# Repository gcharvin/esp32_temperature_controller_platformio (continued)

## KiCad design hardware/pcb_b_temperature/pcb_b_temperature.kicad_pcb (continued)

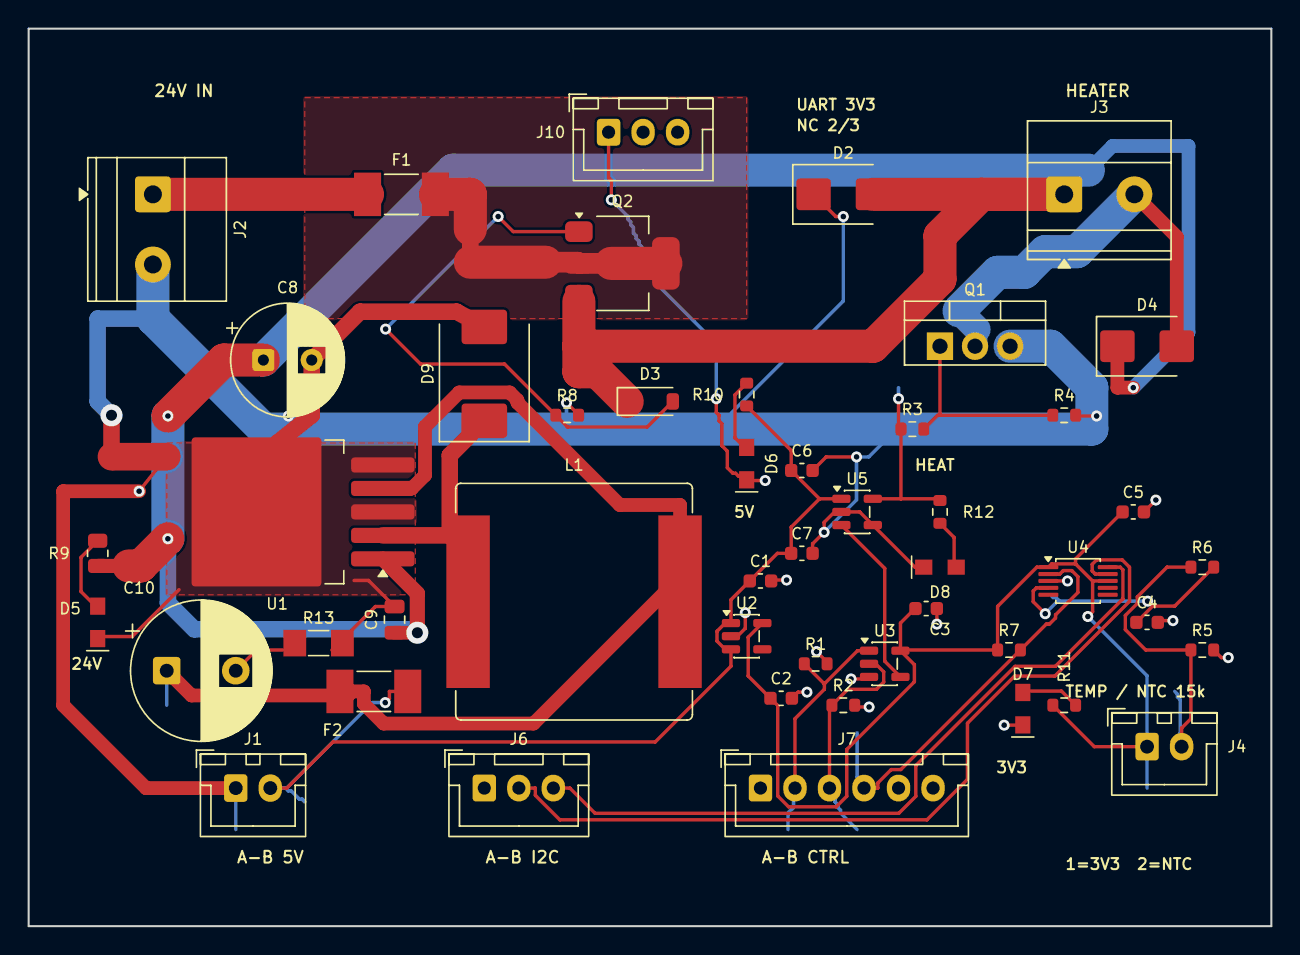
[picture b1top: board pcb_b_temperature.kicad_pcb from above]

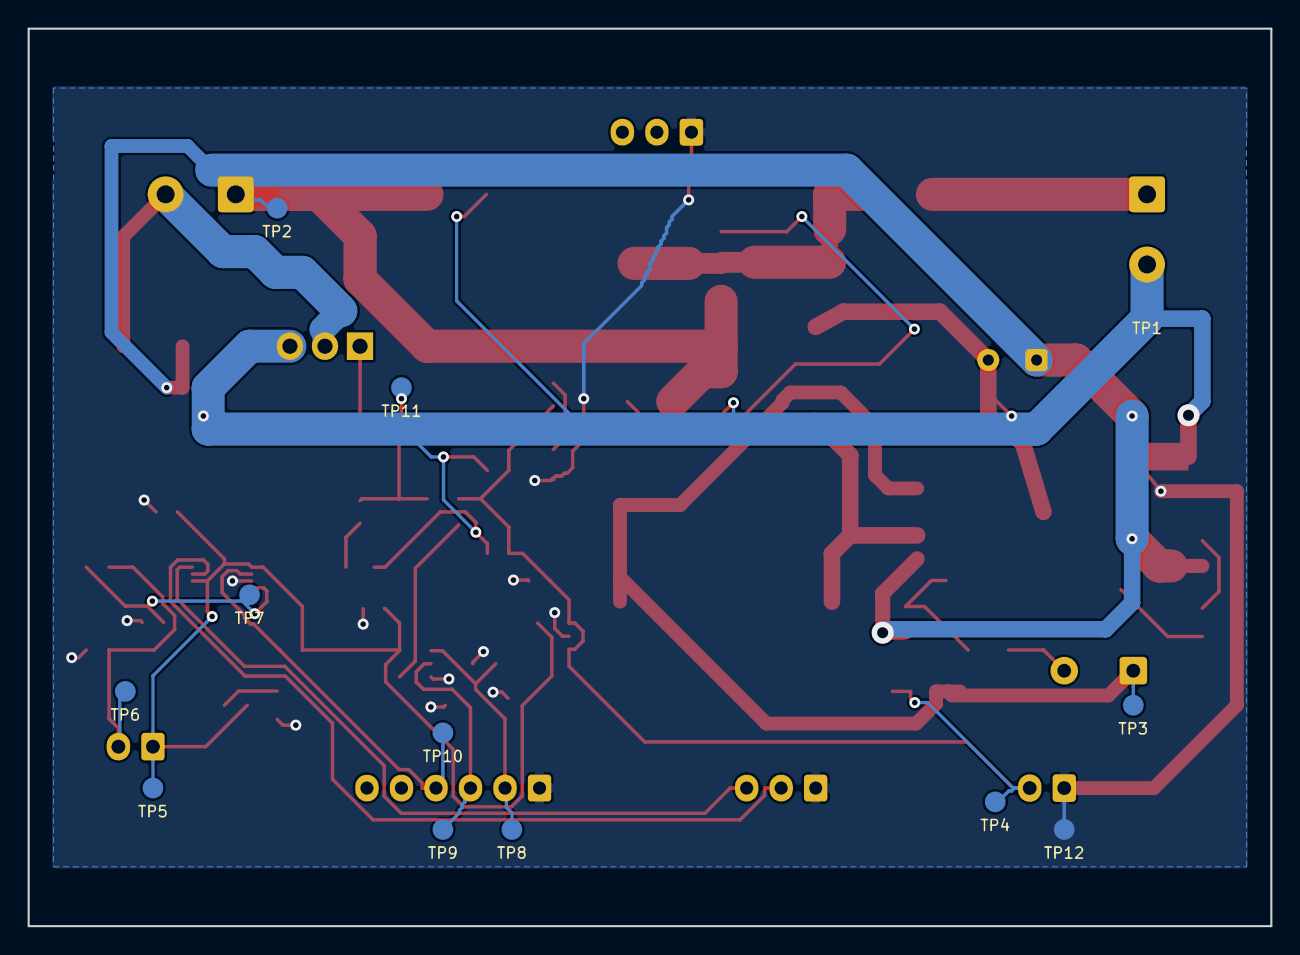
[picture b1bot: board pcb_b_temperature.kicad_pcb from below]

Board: 2 copper layers, 90.0 x 65.0 mm, 61 parts (12 on the bottom side), 26 nets.

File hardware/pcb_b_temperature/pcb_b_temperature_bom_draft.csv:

Reference,Value,Footprint,Design_Status,MPN,Manufacturer
C1,1uF / 16V X7R,Capacitor_SMD:C_0603_1608Metric,ENGINEERING_SELECTED_STOCK_REVISION_2026_11_10,0603B105K160CT,Walsin
C2,1uF / 10V X7R,Capacitor_SMD:C_0603_1608Metric,ENGINEERING_SELECTED_STOCK_REVISION_2026_11_10,0603B105K160CT,Walsin
C3,100nF / 10V X7R,Capacitor_SMD:C_0603_1608Metric,ENGINEERING_SELECTED_FOR_PROTOTYPE,C0603C104K4RACTU,KEMET / Yageo Group
C4,100nF / 10V X7R,Capacitor_SMD:C_0603_1608Metric,ENGINEERING_SELECTED_FOR_PROTOTYPE,C0603C104K4RACTU,KEMET / Yageo Group
C5,100nF / 10V X7R,Capacitor_SMD:C_0603_1608Metric,ENGINEERING_SELECTED_FOR_PROTOTYPE,C0603C104K4RACTU,KEMET / Yageo Group
C6,100nF / 16V X7R,Capacitor_SMD:C_0603_1608Metric,ENGINEERING_SELECTED_FOR_PROTOTYPE,C0603C104K4RACTU,KEMET / Yageo Group
C7,1uF / 16V X7R,Capacitor_SMD:C_0603_1608Metric,ENGINEERING_SELECTED_STOCK_REVISION_2026_11_10,0603B105K160CT,Walsin
C8,100uF / 50V / EEUFR1H101,Capacitor_THT:CP_Radial_D8.0mm_P3.50mm,ENGINEERING_SELECTED_FOR_PROTOTYPE,EEUFR1H101,Panasonic
C9,100nF / 50V X7R,Capacitor_SMD:C_0805_2012Metric,ENGINEERING_SELECTED_FOR_PROTOTYPE,C0805C104K5RACTU,KEMET / Yageo Group
C10,330uF / 35V,LabHardware:CP_Radial_EEUFS1V331LB_P5_D10_Keepout,ENGINEERING_SELECTED_STOCK_REVISION_2026_11_10,EEUFS1V331LB,Panasonic
D2,SMBJ24CA / transients NOT qualified,Diode_SMD:D_SMB,ENGINEERING_SELECTED_FOR_PROTOTYPE,SMBJ24CA,Littelfuse
D3,BZT52C12 / 12V gate clamp,Diode_SMD:D_SOD-123,ENGINEERING_SELECTED_FOR_PROTOTYPE,BZT52C12-7-F,Diodes Incorporated
D4,STPS5L60U / cable flyback,Diode_SMD:D_SMB,ENGINEERING_SELECTED_FOR_PROTOTYPE,STPS5L60U,STMicroelectronics
D5,APT2012LZGCK,LabHardware:LED_Kingbright_APT2012_Manufacturer,ENGINEERING_SELECTED_FOR_PROTOTYPE,APT2012LZGCK,Kingbright
D6,APT2012LZGCK,LabHardware:LED_Kingbright_APT2012_Manufacturer,ENGINEERING_SELECTED_FOR_PROTOTYPE,APT2012LZGCK,Kingbright
D7,APT2012LZGCK,LabHardware:LED_Kingbright_APT2012_Manufacturer,ENGINEERING_SELECTED_FOR_PROTOTYPE,APT2012LZGCK,Kingbright
D8,APT2012LSYCK/J3-PRV,LabHardware:LED_Kingbright_APT2012_Manufacturer,ENGINEERING_SELECTED_STOCK_REVISION_2026_11_10,APT2012LSYCK/J3-PRV,Kingbright
D9,SS36 / 60V 3A,Diode_SMD:D_SMC,ENGINEERING_SELECTED_FOR_PROTOTYPE,SS36-E3/57T,Vishay
F1,6.3A / 125VDC / 045106.3MRL,Fuse:Fuse_Littelfuse-NANO2-451_453,ENGINEERING_SELECTED_FOR_PROTOTYPE,045106.3MRL,Littelfuse
F2,1A / 125VDC / 0451001.MRL,Fuse:Fuse_Littelfuse-NANO2-451_453,ENGINEERING_SELECTED_FOR_PROTOTYPE,0451001.MRL,Littelfuse
J1,A-B POWER / XH-2,Connector_JST:JST_XH_B2B-XH-A_1x02_P2.50mm_Vertical,ENGINEERING_SELECTED_FOR_PROTOTYPE,B2B-XH-A(LF)(SN),JST
J2,24V IN / + PGND,"TerminalBlock_Phoenix:TerminalBlock_Phoenix_MKDS-1,5-2-5.08_1x02_P5.08mm_Horizontal",ENGINEERING_SELECTED_FOR_PROTOTYPE,1715721,Phoenix Contact
J3,HEATER / + switched return,"TerminalBlock_Phoenix:TerminalBlock_Phoenix_MKDS-1,5-2-5.08_1x02_P5.08mm_Horizontal",ENGINEERING_SELECTED_FOR_PROTOTYPE,1715721,Phoenix Contact
J4,TEMP / NTC 15k B3920,Connector_JST:JST_XH_B2B-XH-A_1x02_P2.50mm_Vertical,ENGINEERING_SELECTED_FOR_PROTOTYPE,B2B-XH-A(LF)(SN),JST
J6,A-B I2C / XH-3,Connector_JST:JST_XH_B3B-XH-A_1x03_P2.50mm_Vertical,ENGINEERING_SELECTED_FOR_PROTOTYPE,B3B-XH-A(LF)(SN),JST
J7,A-B CTRL / XH-6,Connector_JST:JST_XH_B6B-XH-A_1x06_P2.50mm_Vertical,ENGINEERING_SELECTED_FOR_PROTOTYPE,B6B-XH-A(LF)(SN),JST
L1,100uH / SRP1770TA-101M,Inductor_SMD:L_Bourns_SRP1770TA_16.9x16.9mm,ENGINEERING_SELECTED_FOR_PROTOTYPE,SRP1770TA-101M,Bourns
NT1,GND STAR / NO COMPONENT,NetTie:NetTie-2_SMD_Pad2.0mm,NOT_A_FACTORY_PURCHASED_NATIVE_PART,,
Q1,IRLZ44NPBF / gate 5 V,Package_TO_SOT_THT:TO-220-3_Vertical,ENGINEERING_SELECTED_FOR_PROTOTYPE,IRLZ44NPBF,Infineon
Q2,DMP6023LE-13 / reverse input,Package_TO_SOT_SMD:SOT-223-3_TabPin2,ENGINEERING_SELECTED_FOR_PROTOTYPE,DMP6023LE-13,Diodes Incorporated
R1,47k,Resistor_SMD:R_0603_1608Metric,ENGINEERING_SELECTED_FOR_PROTOTYPE,RC0603FR-0747KL,YAGEO
R2,47k,Resistor_SMD:R_0603_1608Metric,ENGINEERING_SELECTED_FOR_PROTOTYPE,RC0603FR-0747KL,YAGEO
R3,22R,Resistor_SMD:R_0603_1608Metric,ENGINEERING_SELECTED_FOR_PROTOTYPE,RC0603FR-0722RL,YAGEO
R4,100k,Resistor_SMD:R_0603_1608Metric,ENGINEERING_SELECTED_FOR_PROTOTYPE,RC0603FR-07100KL,YAGEO
R5,8.45k 1%,Resistor_SMD:R_0603_1608Metric,ENGINEERING_SELECTED_FOR_PROTOTYPE,RC0603FR-078K45L,YAGEO
R6,1k,Resistor_SMD:R_0603_1608Metric,ENGINEERING_SELECTED_FOR_PROTOTYPE,RC0603FR-071KL,YAGEO
R7,10k,Resistor_SMD:R_0603_1608Metric,ENGINEERING_SELECTED_FOR_PROTOTYPE,RC0603FR-0710KL,YAGEO
R8,100k,Resistor_SMD:R_0603_1608Metric,ENGINEERING_SELECTED_FOR_PROTOTYPE,RC0603FR-07100KL,YAGEO
R9,15k / 1% / 0.125W,Resistor_SMD:R_0805_2012Metric,ENGINEERING_SELECTED_FOR_PROTOTYPE,RC0805FR-0715KL,YAGEO
R10,1.5k / 1% / 0.1W,Resistor_SMD:R_0603_1608Metric,ENGINEERING_SELECTED_FOR_PROTOTYPE,RC0603FR-071K5L,YAGEO
R11,470R / 1% / 0.1W,Resistor_SMD:R_0603_1608Metric,ENGINEERING_SELECTED_FOR_PROTOTYPE,RC0603FR-07470RL,YAGEO
R12,2.2k / 1% / 0.1W,Resistor_SMD:R_0603_1608Metric,ENGINEERING_SELECTED_FOR_PROTOTYPE,RC0603FR-072K2L,YAGEO
R13,50m / 1% / 0.25W,LabHardware:Vishay_WSL1206_6m_to_200m,ENGINEERING_SELECTED_STOCK_REVISION_2026_11_10,WSL1206R0500FEA,Vishay
U1,LM2596S-5.0/NOPB,Package_TO_SOT_SMD:TO-263-5_TabPin3,ENGINEERING_SELECTED_FOR_PROTOTYPE,LM2596S-5.0/NOPB,Texas Instruments
U2,AP2112K-3.3,Package_TO_SOT_SMD:SOT-23-5,ENGINEERING_SELECTED_FOR_PROTOTYPE,AP2112K-3.3TRG1,Diodes Incorporated
U3,SN74LVC1G08DBVR,Package_TO_SOT_SMD:SOT-23-5,ENGINEERING_SELECTED_FOR_PROTOTYPE,SN74LVC1G08DBVR,Texas Instruments
U4,ADS1115IDGSR / 0x49,Package_SO:TSSOP-10_3x3mm_P0.5mm,ENGINEERING_SELECTED_FOR_PROTOTYPE,ADS1115IDGSR,Texas Instruments
U5,UCC27517DBVR,Package_TO_SOT_SMD:SOT-23-5,ENGINEERING_SELECTED_FOR_PROTOTYPE,UCC27517DBVR,Texas Instruments
TP1,PGND,LabHardware:ProbePad_D1.5mm_NoPaste,COPPER_ONLY_TEST_POINT,,
TP2,VIN_PROTECTED,LabHardware:ProbePad_D1.5mm_NoPaste,COPPER_ONLY_TEST_POINT,,
TP3,+5V_BUCK,LabHardware:ProbePad_D1.5mm_NoPaste,COPPER_ONLY_TEST_POINT,,
TP4,+5V_AB,LabHardware:ProbePad_D1.5mm_NoPaste,COPPER_ONLY_TEST_POINT,,
TP5,+3V3_B,LabHardware:ProbePad_D1.5mm_NoPaste,COPPER_ONLY_TEST_POINT,,
TP6,NTC_RAW,LabHardware:ProbePad_D1.5mm_NoPaste,COPPER_ONLY_TEST_POINT,,
TP7,NTC_ADC,LabHardware:ProbePad_D1.5mm_NoPaste,COPPER_ONLY_TEST_POINT,,
TP8,PWM0,LabHardware:ProbePad_D1.5mm_NoPaste,COPPER_ONLY_TEST_POINT,,
TP9,ENABLE,LabHardware:ProbePad_D1.5mm_NoPaste,COPPER_ONLY_TEST_POINT,,
TP10,FAULT_N,LabHardware:ProbePad_D1.5mm_NoPaste,COPPER_ONLY_TEST_POINT,,
TP11,GATE_DRV,LabHardware:ProbePad_D1.5mm_NoPaste,COPPER_ONLY_TEST_POINT,,
TP12,GND,LabHardware:ProbePad_D1.5mm_NoPaste,COPPER_ONLY_TEST_POINT,,
J10,A-B UART / 3V3 / GND TX_A RX_A,Connector_JST:JST_XH_B3B-XH-A_1x03_P2.50mm_Vertical,ENGINEERING_SELECTED_FOR_PROTOTYPE,B3B-XH-A(LF)(SN),JST

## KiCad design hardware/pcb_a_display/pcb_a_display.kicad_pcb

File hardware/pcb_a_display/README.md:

# Carte A v0.4 — hôte commun et affichage

Ouvrir `pcb_a_display.kicad_pro` puis le PCB ou le schéma. Format110×75×1,6mm,
deux couches35µm, réserves mécaniques et antenne conservées.

La préparation finale utilise deux sockets **HCTL PM254-1-15-Z-8.5**,15 contacts
chacun, pas2,54mm, rangées25,40mm confirmées par l'utilisateur. L'empreinte
locale `LabHardware:ESP32_30P_HCTL_PM254_Rows25.40mm` emploie des trous
nominaux1,05mm et des zones de dégagement dimensionnées pour les boîtiers HCTL. La DevKit
reste amovible, fournie par l'utilisateur ; ses trois variantes partagent le
brochage confirmé. Le nom historique diymore/ASSUMED n'est plus l'empreinte active.

Les MPN/fabricants des composants à assembler sont inscrits dans KiCad et
contrôlés avec `../manufacturing/component_selection.json`. Les voyants
emploient les pastilles recommandées Kingbright, cathode1. Le fabricant
soude les CMS, JST, JP1 et les deux sockets ; le cavalier JP1 est livré séparé.

J1 = **1GND,2+5V régulé**. Ne pas appliquer12V ou24V à cette carte. J6 I²C =
1GND,2SDA,3SCL ; J7 =1GND,2PWM0,3ENABLE,4FAULT_N,5PWM1,6DIN0. Les périphériques
I²C sur J2/J4/J5 utilisent1GND,2+3V3_A,3SDA,4SCL ; J3 encodeur utilise
1A,2B,3bouton,4GND. Voir les schémas et le tableau de faisceaux pour le câblage.

USB seul pour le service : sources externes coupées, J1/J6/J7 débranchés,
JP1 retiré. JP1 ne gère pas automatiquement VBUS/VIN. Les circuits USB des
DevKit et leur hauteur réelle restent des vérifications d'intégration.

La maquette v0.12 inclut les sockets maximaux documentés et une enveloppe
d'entretoise mâle2,54mm. Voir le [dossier de fabrication](../manufacturing/START_HERE.md)
pour les plans, le routage, le contrôle usine et les accords externes requis.

## Révision diagnostic du 6 novembre 2026

Les pastilles TP au dos sont du cuivre seul, sans pâte ni pièce à acheter.
Voir [le plan de mesure](../TEST_POINTS.md) et le firmware autonome dans
`../../firmware/diagnostic/`. Les pistes antérieures et le circuit de puissance
sont conservés ; le diagnostic maintient ENABLE à zéro.

## Extension UART du 10 novembre 2026

Révisions **A0.4.3 / B0.5.3** : J10 est un JST-XH3 supplémentaire assemblé
sur chaque PCB, pas2,50mm, même MPN B3B-XH-A(LF)(SN) que J6.

| Broche J10 | Carte A | Carte B température |
| --- | --- | --- |
| 1 | GND | GND |
| 2 | TX_A, GPIO17, pad U1.22 | Non connectée ; réserve RX de future B |
| 3 | RX_A, GPIO16, pad U1.21 | Non connectée ; réserve TX de future B |

Câblage **droit 1→1, 2→2, 3→3** ; TX/RX sont nommés du point de vue de A.
UART logique **3,3V**, sans alimentation dans ce connecteur : jamais RS232
ni5V directement. Les transceivers RS232/RS485 éventuels appartiennent aux
futures B. Le port série USB de la DevKit reste indépendant ; les deux PWM
et ENABLE/FAULT_N/DIN0 restent disponibles. GPIO16/17 doivent être libres
sur la variante de DevKit employée (modules à PSRAM utilisant ces broches
non couverts par cette interface). Aucun UART n’est activé par le firmware
de diagnostic actuel ; aucun essai de boucle matérielle n’est déclaré fait.

B température n’a pas de périphérique UART : les deux pastilles sont
intentionnellement NC et le connecteur est néanmoins à souder. Le câble UART
est **facultatif pour ce prototype** et n’est pas ajouté au devis LCSC en cours.
Si nécessaire plus tard, reprendre la construction H02 XHP-3/XHP-3,300mm AWG26
avec un repérage UART distinct. Ne pas confondre J6 I²C et J10 UART, mécaniquement
identiques. Les alias fabricant J8/J9 des deux sockets de A restent inchangés.

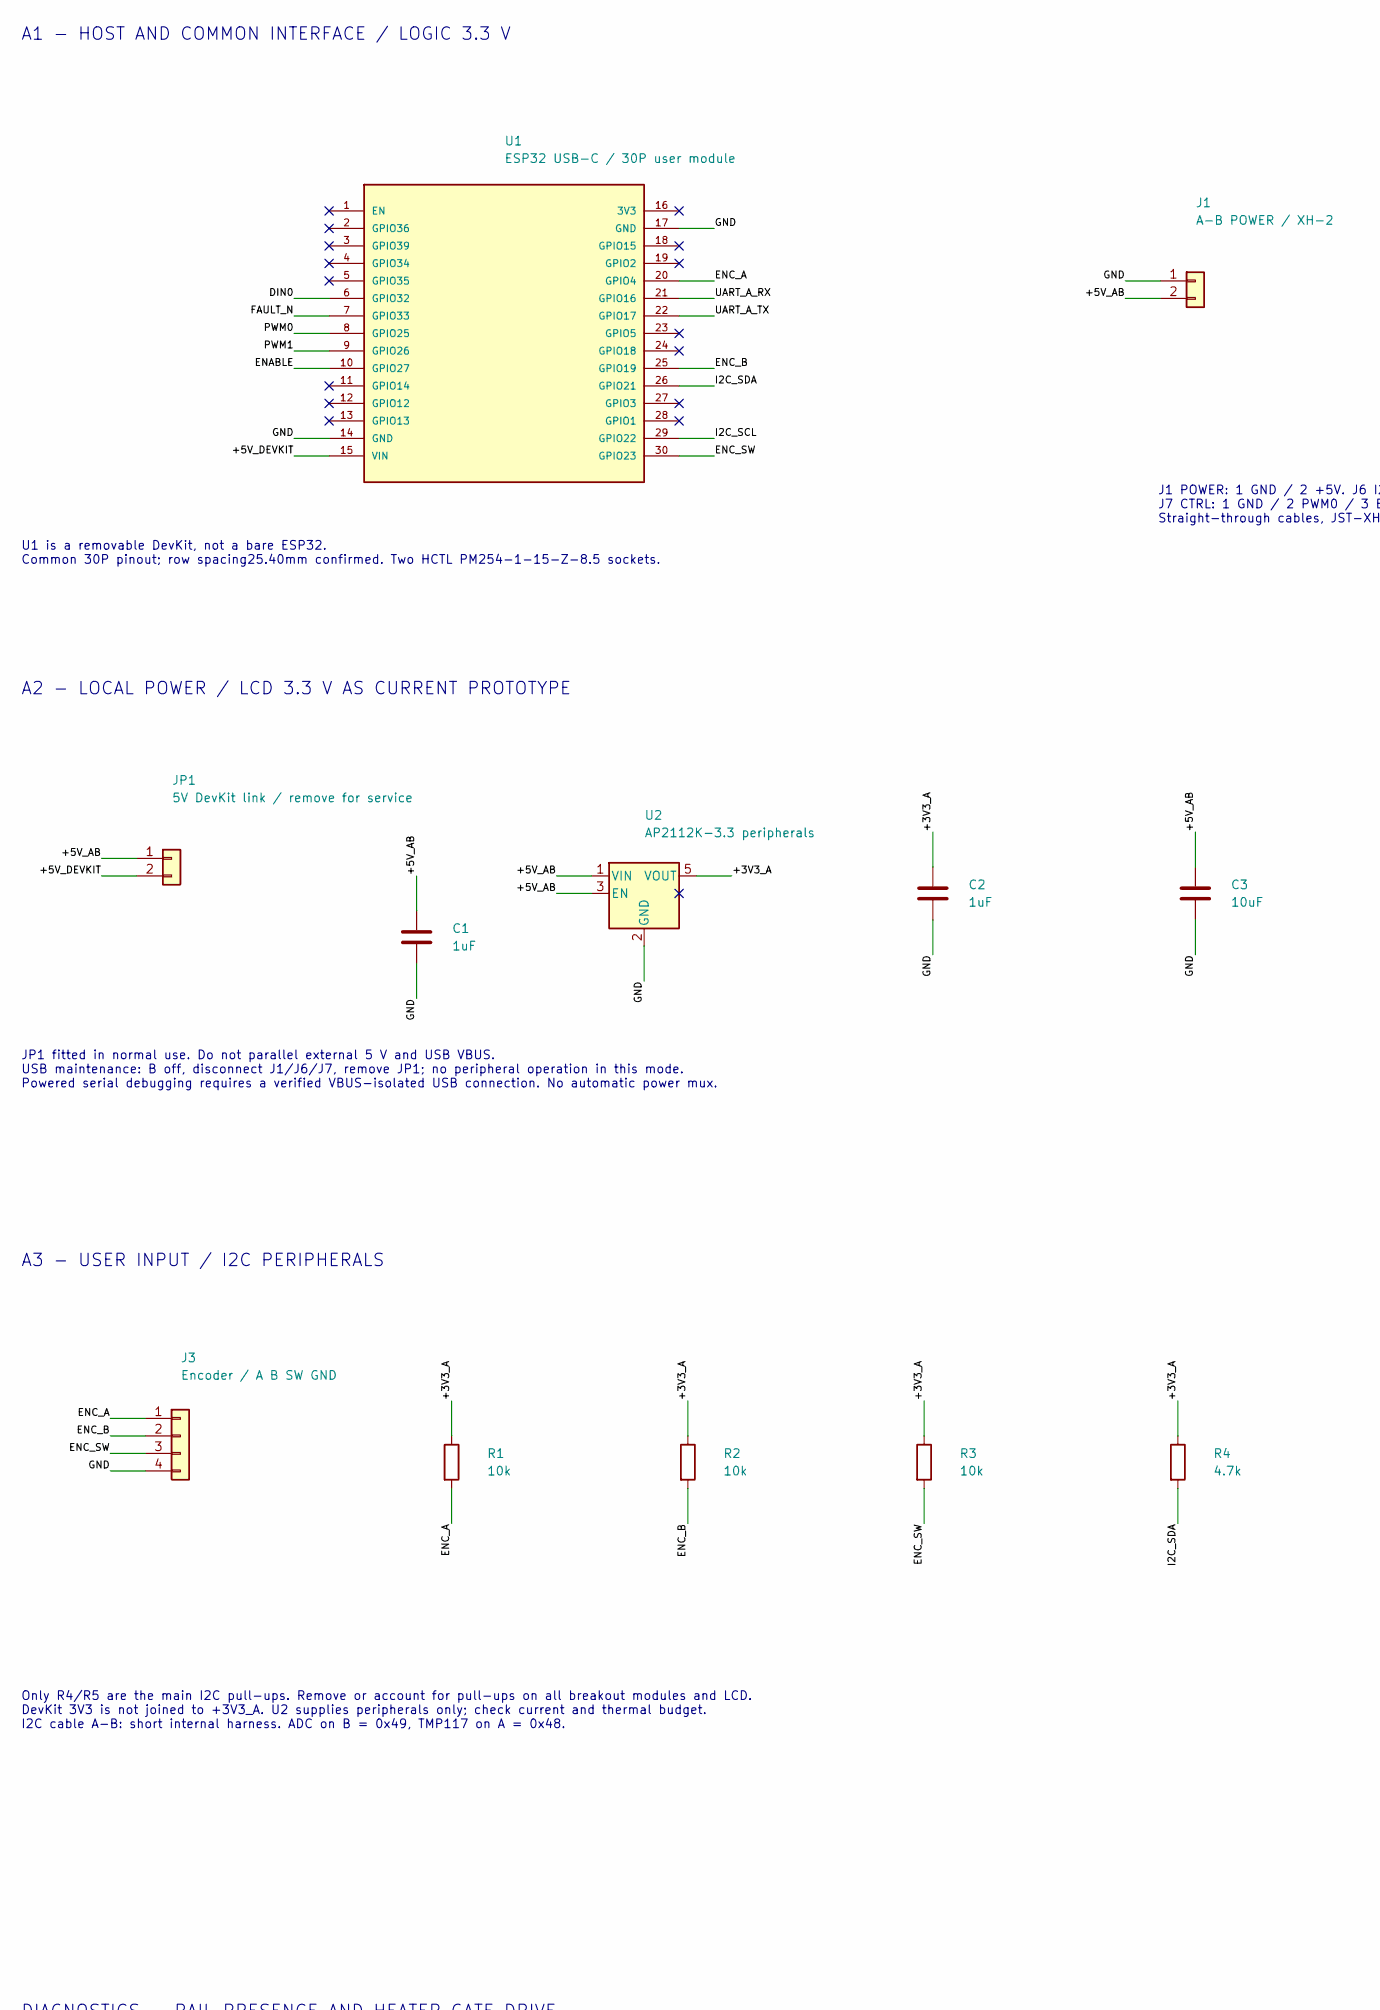
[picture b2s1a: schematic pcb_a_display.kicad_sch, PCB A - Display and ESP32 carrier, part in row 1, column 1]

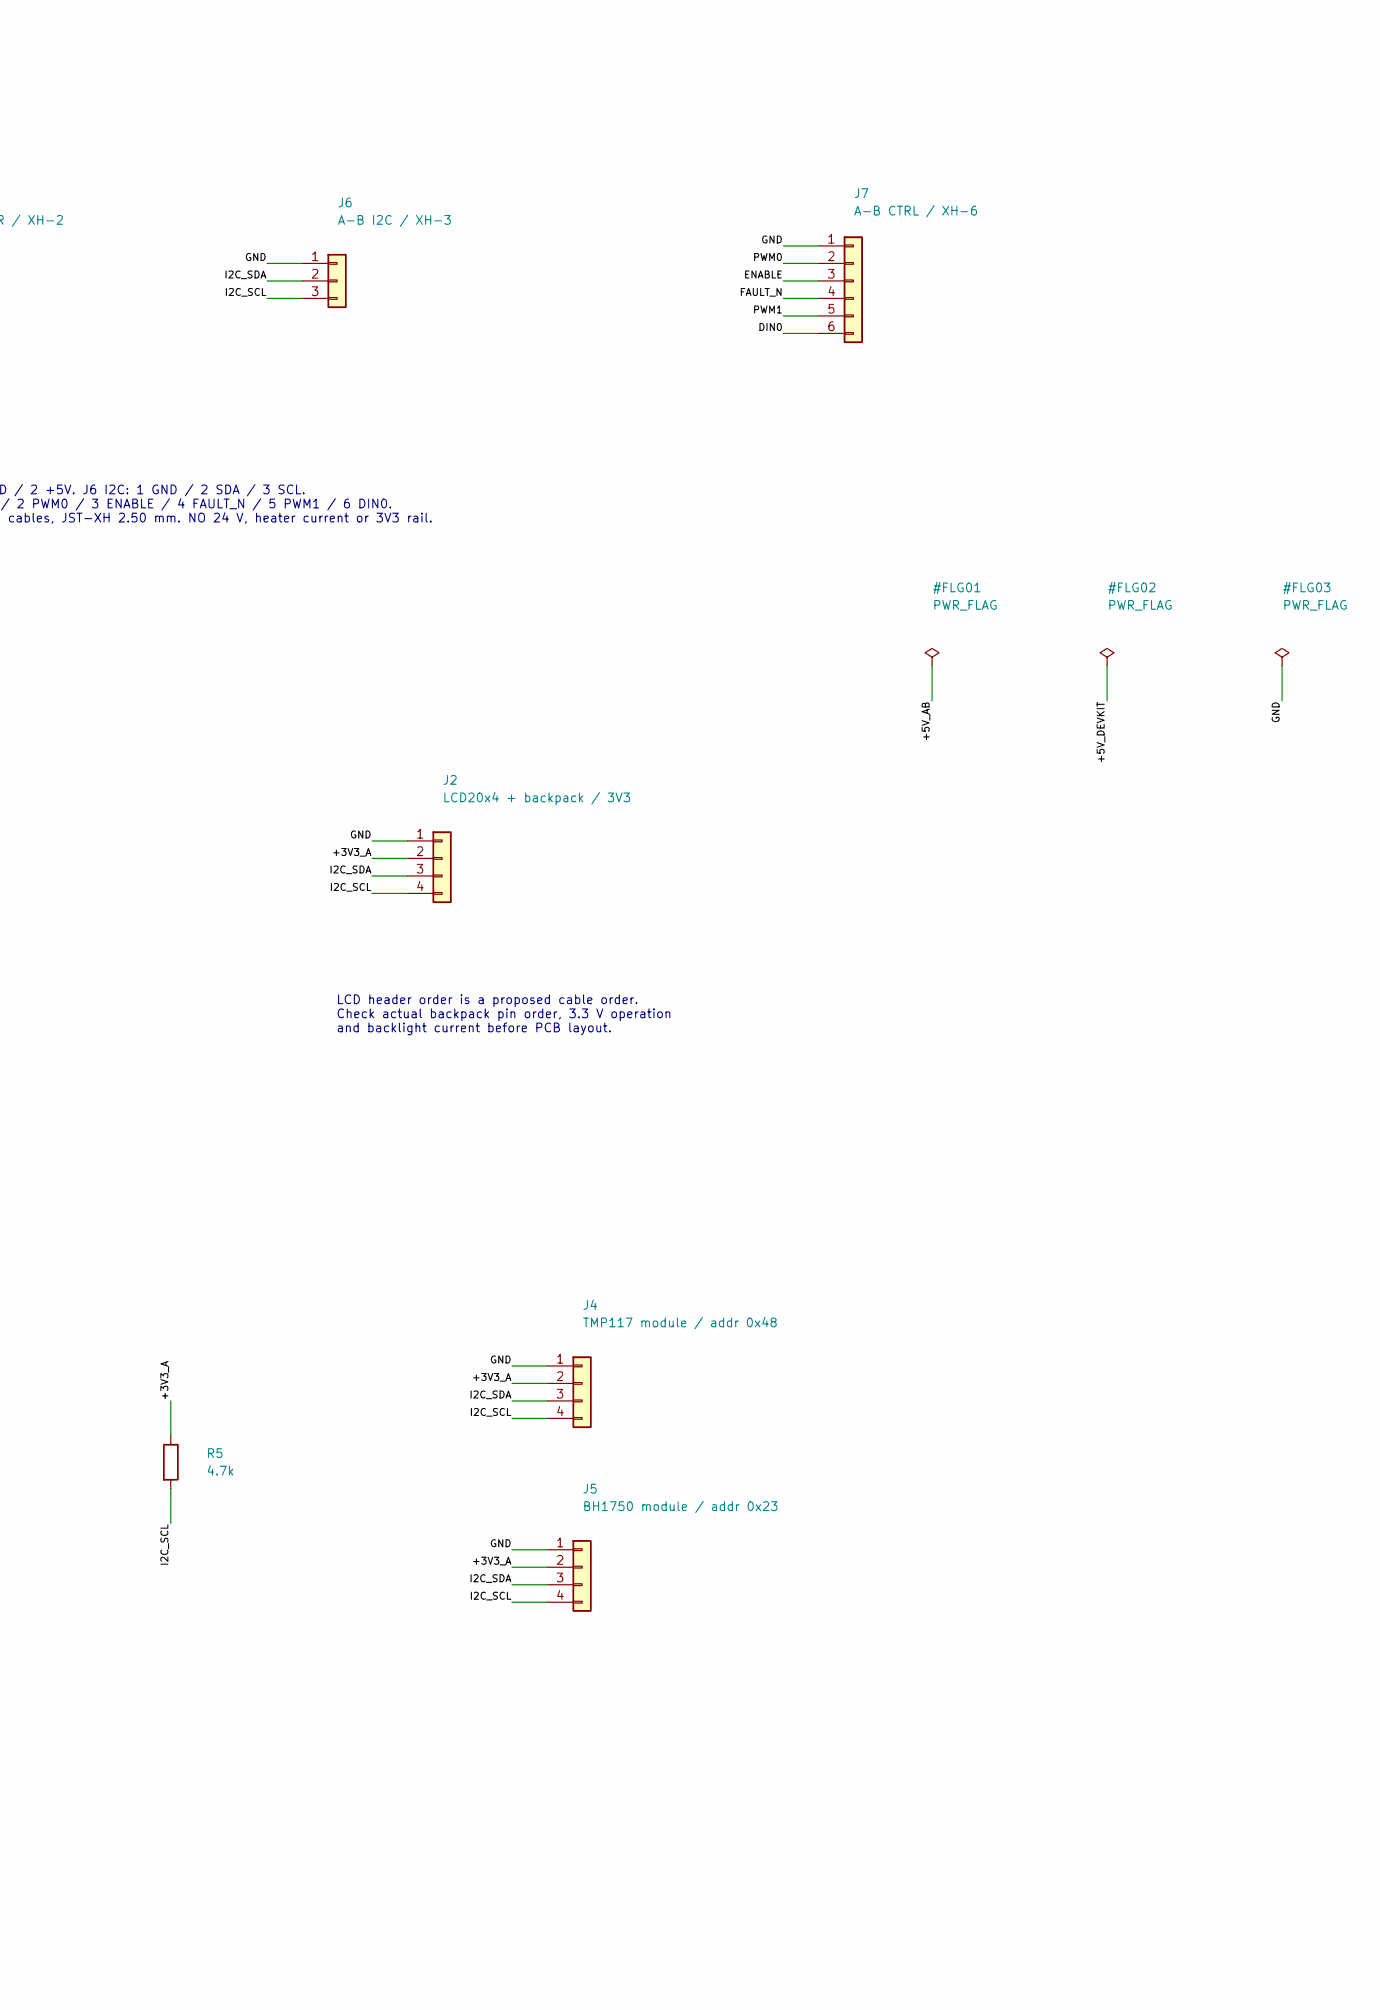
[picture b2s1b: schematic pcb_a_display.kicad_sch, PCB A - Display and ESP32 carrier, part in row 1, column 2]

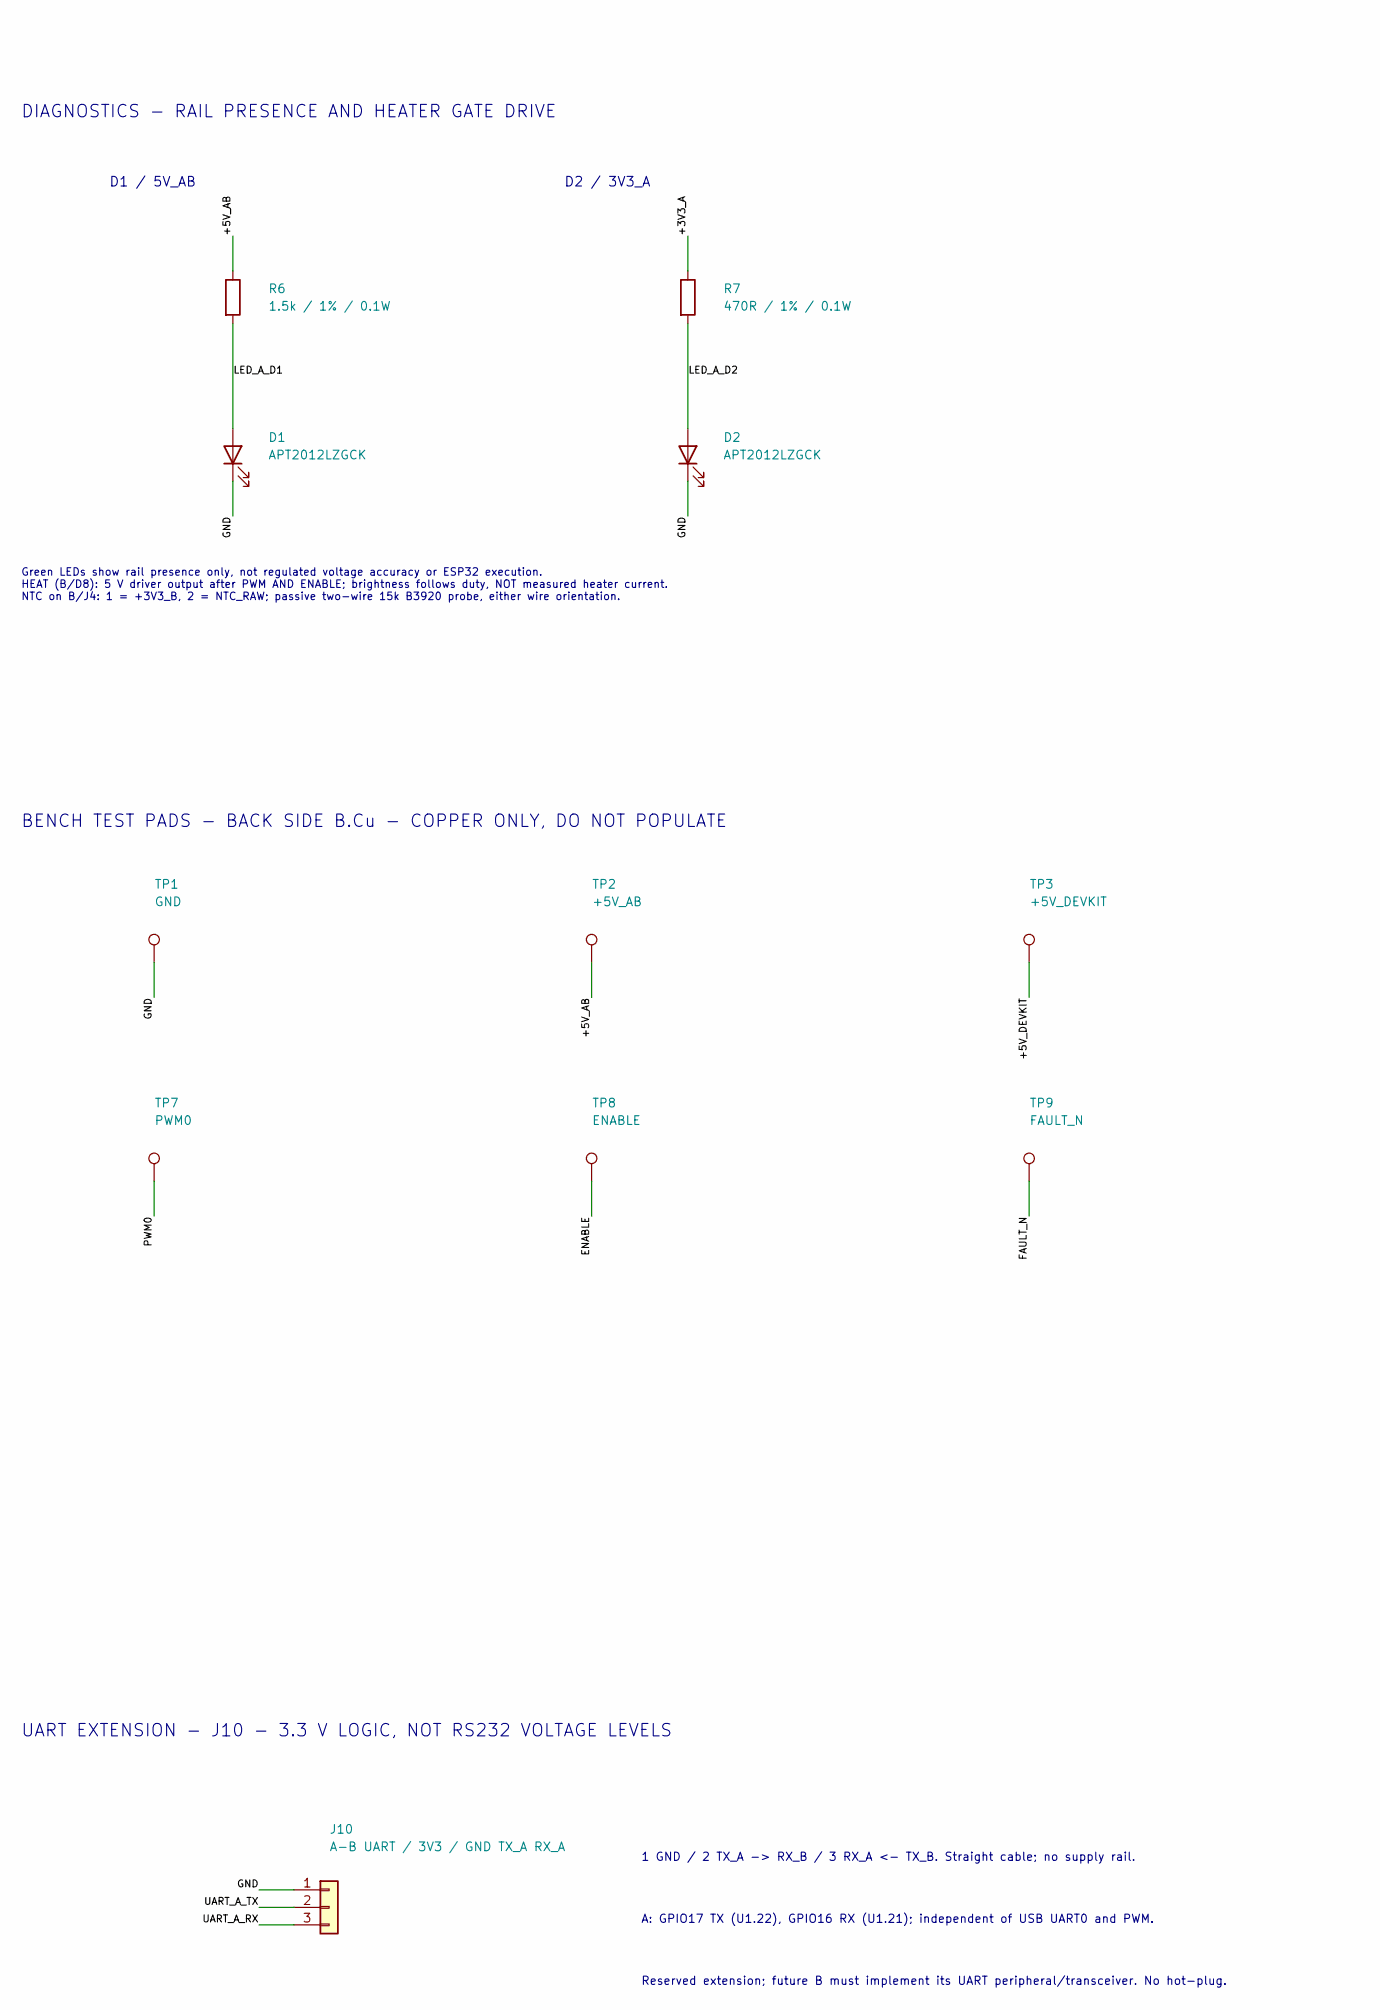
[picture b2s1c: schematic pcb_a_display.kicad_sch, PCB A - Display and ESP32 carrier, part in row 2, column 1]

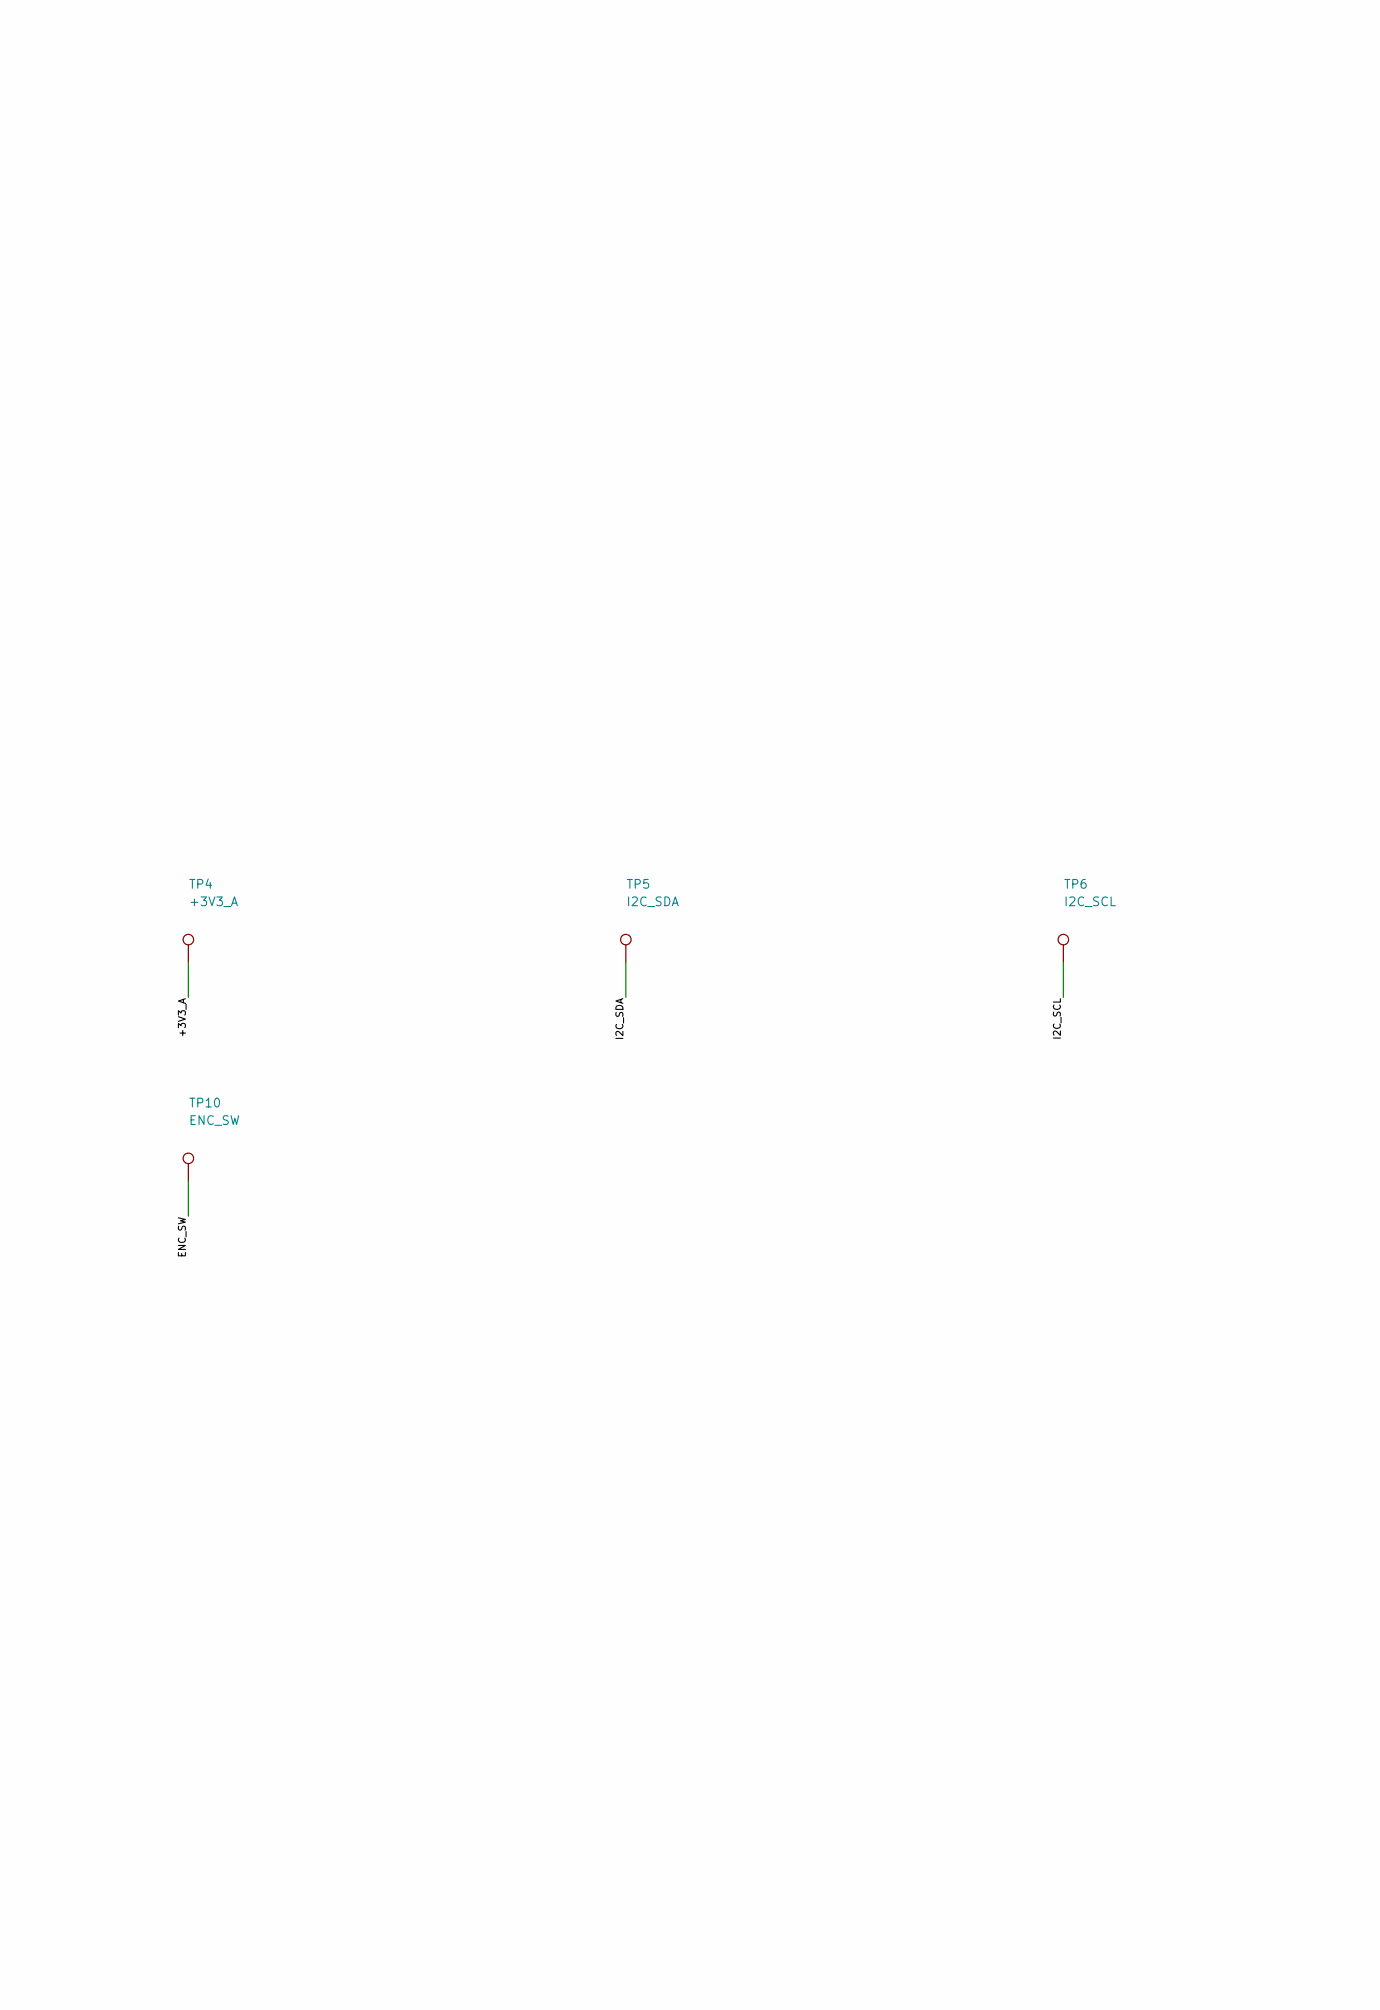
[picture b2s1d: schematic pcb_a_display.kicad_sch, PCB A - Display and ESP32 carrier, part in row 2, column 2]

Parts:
C1, C2: 1uF; C_0603_1608Metric; MPN 0603B105K160CT
C3: 10uF; C_0603_1608Metric; MPN CL10A106KP8NNNC
D1, D2: APT2012LZGCK; LED_Kingbright_APT2012_Manufacturer; MPN APT2012LZGCK
J1: A-B POWER / XH-2; JST_XH_B2B-XH-A_1x02_P2.50mm_Vertical; MPN B2B-XH-A(LF)(SN)
J2: LCD20x4 + backpack / 3V3; JST_XH_B4B-XH-A_1x04_P2.50mm_Vertical; MPN B4B-XH-A(LF)(SN)
J3: Encoder / A B SW GND; JST_XH_B4B-XH-A_1x04_P2.50mm_Vertical; MPN B4B-XH-A(LF)(SN)
J4: TMP117 module / addr 0x48; JST_XH_B4B-XH-A_1x04_P2.50mm_Vertical; MPN B4B-XH-A(LF)(SN)
J5: BH1750 module / addr 0x23; JST_XH_B4B-XH-A_1x04_P2.50mm_Vertical; MPN B4B-XH-A(LF)(SN)
J6: A-B I2C / XH-3; JST_XH_B3B-XH-A_1x03_P2.50mm_Vertical; MPN B3B-XH-A(LF)(SN)
J7: A-B CTRL / XH-6; JST_XH_B6B-XH-A_1x06_P2.50mm_Vertical; MPN B6B-XH-A(LF)(SN)
J10: A-B UART / 3V3 / GND TX_A RX_A; JST_XH_B3B-XH-A_1x03_P2.50mm_Vertical; MPN B3B-XH-A(LF)(SN)
JP1: 5V DevKit link / remove for service; PinHeader_1x02_P2.54mm_Vertical; MPN M20-9990246
R1, R2, R3: 10k; R_0603_1608Metric; MPN RC0603FR-0710KL
R4, R5: 4.7k; R_0603_1608Metric; MPN RC0603FR-074K7L
R6: 1.5k / 1% / 0.1W; R_0603_1608Metric; MPN RC0603FR-071K5L
R7: 470R / 1% / 0.1W; R_0603_1608Metric; MPN RC0603FR-07470RL
TP1: GND; ProbePad_D1.5mm_NoPaste
TP2: +5V_AB; ProbePad_D1.5mm_NoPaste
TP3: +5V_DEVKIT; ProbePad_D1.5mm_NoPaste
TP4: +3V3_A; ProbePad_D1.5mm_NoPaste
TP5: I2C_SDA; ProbePad_D1.5mm_NoPaste
TP6: I2C_SCL; ProbePad_D1.5mm_NoPaste
TP7: PWM0; ProbePad_D1.5mm_NoPaste
TP8: ENABLE; ProbePad_D1.5mm_NoPaste
TP9: FAULT_N; ProbePad_D1.5mm_NoPaste
TP10: ENC_SW; ProbePad_D1.5mm_NoPaste
U1: ESP32 USB-C / 30P user module; ESP32_30P_HCTL_PM254_Rows25.40mm
U2: AP2112K-3.3 peripherals; SOT-23-5; MPN AP2112K-3.3TRG1

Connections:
/+3V3_A: C2.1, J2.2, J4.2, J5.2, R1.1, R2.1, R3.1, R4.1, R5.1, R7.1, TP4.1, U2.5 (VOUT)
/+5V_AB: C1.1, C3.1, J1.2, JP1.1, R6.1, TP2.1, U2.1 (VIN), U2.3 (EN)
/+5V_DEVKIT: JP1.2, TP3.1, U1.15 (VIN)
/DIN0: J7.6, U1.6 (GPIO32)
/ENABLE: J7.3, TP8.1, U1.10 (GPIO27)
/ENC_A: J3.1, R1.2, U1.20 (GPIO4)
/ENC_B: J3.2, R2.2, U1.25 (GPIO19)
/ENC_SW: J3.3, R3.2, TP10.1, U1.30 (GPIO23)
/FAULT_N: J7.4, TP9.1, U1.7 (GPIO33)
/GND: C1.2, C2.2, C3.2, D1.1 (K), D2.1 (K), J1.1, J2.1, J3.4, J4.1, J5.1, J6.1, J7.1, J10.1, TP1.1, U1.14 (GND), U1.17 (GND), U2.2 (GND)
/I2C_SCL: J2.4, J4.4, J5.4, J6.3, R5.2, TP6.1, U1.29 (GPIO22)
/I2C_SDA: J2.3, J4.3, J5.3, J6.2, R4.2, TP5.1, U1.26 (GPIO21)
/LED_A_D1: D1.2 (A), R6.2
/LED_A_D2: D2.2 (A), R7.2
/PWM0: J7.2, TP7.1, U1.8 (GPIO25)
/PWM1: J7.5, U1.9 (GPIO26)
/UART_A_RX: J10.3, U1.21 (GPIO16)
/UART_A_TX: J10.2, U1.22 (GPIO17)

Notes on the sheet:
A1 - HOST AND COMMON INTERFACE / LOGIC 3.3 V
J1 POWER: 1 GND / 2 +5V. J6 I2C: 1 GND / 2 SDA / 3 SCL. J7 CTRL: 1 GND / 2 PWM0 / 3 ENABLE / 4 FAULT_N / 5 PWM1 / 6 DIN0. Straight-through cables, JST-XH 2.50 mm. NO 24 V, heater current or 3V3 rail.
U1 is a removable DevKit, not a bare ESP32. Common 30P pinout; row spacing25.40mm confirmed. Two HCTL PM254-1-15-Z-8.5 sockets.
A2 - LOCAL POWER / LCD 3.3 V AS CURRENT PROTOTYPE
JP1 fitted in normal use. Do not parallel external 5 V and USB VBUS. USB maintenance: B off, disconnect J1/J6/J7, remove JP1; no peripheral operation in this mode. Powered serial debugging requires a verified VBUS-isolated USB connection. No automatic power mux.
LCD header order is a proposed cable order. Check actual backpack pin order, 3.3 V operation and backlight current before PCB layout.
A3 - USER INPUT / I2C PERIPHERALS
Only R4/R5 are the main I2C pull-ups. Remove or account for pull-ups on all breakout modules and LCD. DevKit 3V3 is not joined to +3V3_A. U2 supplies peripherals only; check current and thermal budget. I2C cable A-B: short internal harness. ADC on B = 0x49, TMP117 on A = 0x48.
DIAGNOSTICS - RAIL PRESENCE AND HEATER GATE DRIVE
D1 / 5V_AB
D2 / 3V3_A
Green LEDs show rail presence only, not regulated voltage accuracy or ESP32 execution. HEAT (B/D8): 5 V driver output after PWM AND ENABLE; brightness follows duty, NOT measured heater current. NTC on B/J4: 1 = +3V3_B, 2 = NTC_RAW; passive two-wire 15k B3920 probe, either wire orientation.
BENCH TEST PADS - BACK SIDE B.Cu - COPPER ONLY, DO NOT POPULATE
UART EXTENSION - J10 - 3.3 V LOGIC, NOT RS232 VOLTAGE LEVELS
1 GND / 2 TX_A -> RX_B / 3 RX_A <- TX_B. Straight cable; no supply rail.
A: GPIO17 TX (U1.22), GPIO16 RX (U1.21); independent of USB UART0 and PWM.
Reserved extension; future B must implement its UART peripheral/transceiver. No hot-plug.
